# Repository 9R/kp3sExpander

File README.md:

# GPIO Expander for KP3S

This PCB is as a replacement for the original LCD-PCB of the KP3S and can be 
installed in the same location. It will expose additional GPIOs. It is meant
to be used with alternative firmware like klipper, where the original LCD-PCB 
can not be used.

## Features

* exposes SPI2 (can be used to connect a klipper compatible display)
* exposes 23 additional GPIOs
* access to 5V, 3.3V and GND to power additional, low current sensors
* the original flexible flat cable can be used to connect to the mainboard

## Required Parts

* 1x 32 pin FFC connector (bottom contact, 1mm pitch)

optional:
* pin/socket headers (2.54 pitch, 2x 6x2 + 1x 14x2 for full assembly)
* 15cm 32 pin flexible flat cable (pitch 1mm)

## Example Config

An example config for klipper with an SSD1306 OLED display and a rotary encoder 
can be found [here](https://github.com/9R/Klipper_KP3S).

## Manufacturing

Use [KiCAD](https://kicad.org) to generate production files for the manufacturer
of your choice.

## Pictures

#### Top

#### Bottom

#### Next to original LCD-PCB

#### Installed in KP3S

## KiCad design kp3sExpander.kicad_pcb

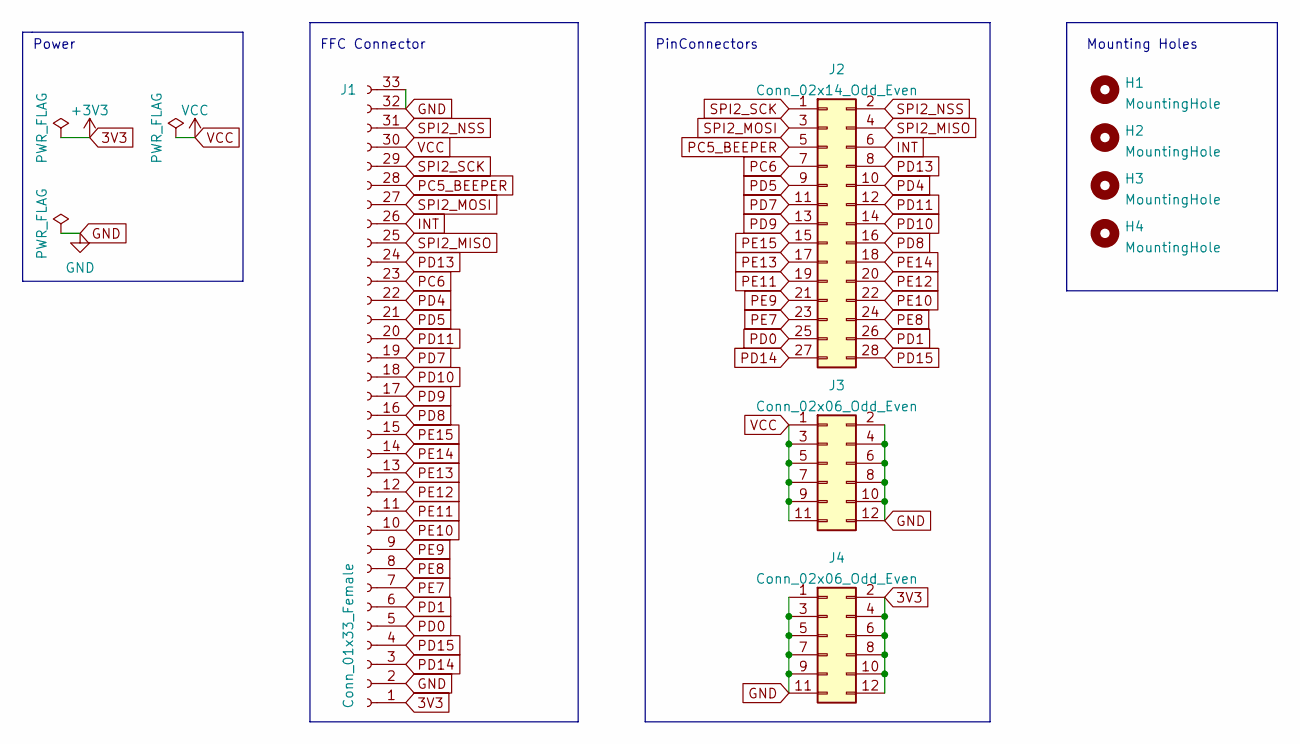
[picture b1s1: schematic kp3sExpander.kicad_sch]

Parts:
H1, H2, H3, H4: MountingHole; MountingHole_3.2mm_M3_DIN965_Pad
J1: Conn_01x33_Female; FPC_32
J2: Conn_02x14_Odd_Even; PinSocket_2x14_P2.54mm_Horizontal
J3, J4: Conn_02x06_Odd_Even; PinHeader_2x06_P2.54mm_Horizontal

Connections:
3V3: J1.1, J4.2, J4.4, J4.6, J4.8, J4.10, J4.12
GND: J1.2, J1.32, J1.33, J3.2, J3.4, J3.6, J3.8, J3.10, J3.12, J4.1, J4.3, J4.5, J4.7, J4.9, J4.11
INT: J1.26, J2.6
PC5_BEEPER: J1.28, J2.5
PC6: J1.23, J2.7
PD0: J1.5, J2.25
PD1: J1.6, J2.26
PD4: J1.22, J2.10
PD5: J1.21, J2.9
PD7: J1.19, J2.11
PD8: J1.16, J2.16
PD9: J1.17, J2.13
PD10: J1.18, J2.14
PD11: J1.20, J2.12
PD13: J1.24, J2.8
PD14: J1.3, J2.27
PD15: J1.4, J2.28
PE7: J1.7, J2.23
PE8: J1.8, J2.24
PE9: J1.9, J2.21
PE10: J1.10, J2.22
PE11: J1.11, J2.19
PE12: J1.12, J2.20
PE13: J1.13, J2.17
PE14: J1.14, J2.18
PE15: J1.15, J2.15
SPI2_MISO: J1.25, J2.4
SPI2_MOSI: J1.27, J2.3
SPI2_NSS: J1.31, J2.2
SPI2_SCK: J1.29, J2.1
VCC: J1.30, J3.1, J3.3, J3.5, J3.7, J3.9, J3.11

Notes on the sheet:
PinConnectors
Power
Mounting Holes
FFC Connector

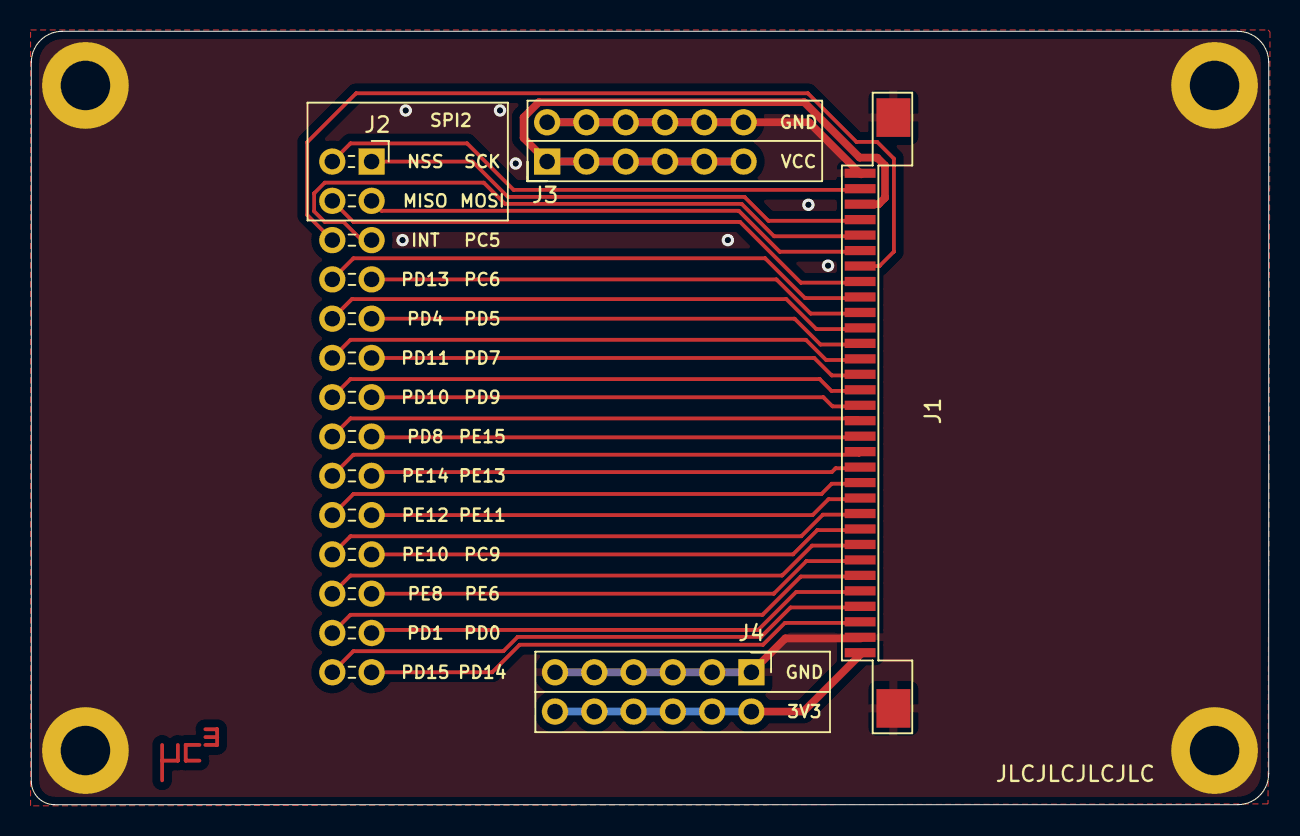
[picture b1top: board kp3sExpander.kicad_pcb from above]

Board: 2 copper layers, 80.0 x 50.0 mm, 8 parts (0 on the bottom side), 31 nets.

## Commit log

2022-05-28 finalize v0.1
2022-05-29 add README.md
2022-05-29 add .gitignore
2022-05-29 add better images
2022-05-29 add export path
2022-05-29 improve README.md
